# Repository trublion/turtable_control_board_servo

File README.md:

## Description

HW control board for turntable. Controls a Teknic Clearpath servo motor, reads an analog audio signal envelope.

## Links (datasheets and documentation)

[IEC plug](https://www.schurter.com/en/datasheet/typ_6765.pdf)
[Potentiometer RK09L](https://tech.alpsalpine.com/prod/e/pdf/potentiometer/rotarypotentiometers/rk09l/rk09l.pdf)  
[Neutrik combo](https://www.neutrik.com/en/product/nj3fp6c.pdf)  

[Clearpath documentation and software](https://www.teknic.com/downloads/)  
Motor user's manual : ClearPath-MC and -SD Series User manual  
Software : ClearPath-MC and -SD Series Motor Setup Program (MSP)  
Mechanical drawings : NEMA 23xx Clearpath Motor familly  
[74HCT4066](https://assets.nexperia.com/documents/data-sheet/74HC_HCT4066.pdf)
[Shunt resistors](https://www.te.com/commerce/DocumentDelivery/DDEController?Action=showdoc&DocId=Data+Sheet%7F9-1773463-7%7FG%7Fpdf%7FEnglish%7FENG_DS_9-1773463-7_G.pdf%7FCAT-C339-A76B)
[BAS21 small signal diode](https://www.vishay.com/docs/85540/bas19.pdf)
[Zener diodes](https://assets.nexperia.com/documents/data-sheet/BZX84_SER.pdf)
[Electrolytic capacitors](https://industrial.panasonic.com/cdbs/www-data/pdf/RDE0000/ABA0000C1181.pdf)
[LM358 comparator](https://www.ti.com/lit/ds/symlink/lm158-n.pdf)
[LM833 operational amplifier](https://www.ti.com/lit/ds/symlink/lm833-n.pdf)
[LM2674 DCDC controller](https://www.ti.com/lit/ds/symlink/lm2674.pdf)
[MBRS3100T3G Schottky power diode](https://www.onsemi.com/pdf/datasheet/mbrs3100t3-d.pdf)
[RS2 power diode](https://www.semiee.com/file/ELMX/MULTICOMP-RS2A.pdf)
[Power inductor](https://www.bourns.com/docs/Product-Datasheets/SRR0735A.pdf)

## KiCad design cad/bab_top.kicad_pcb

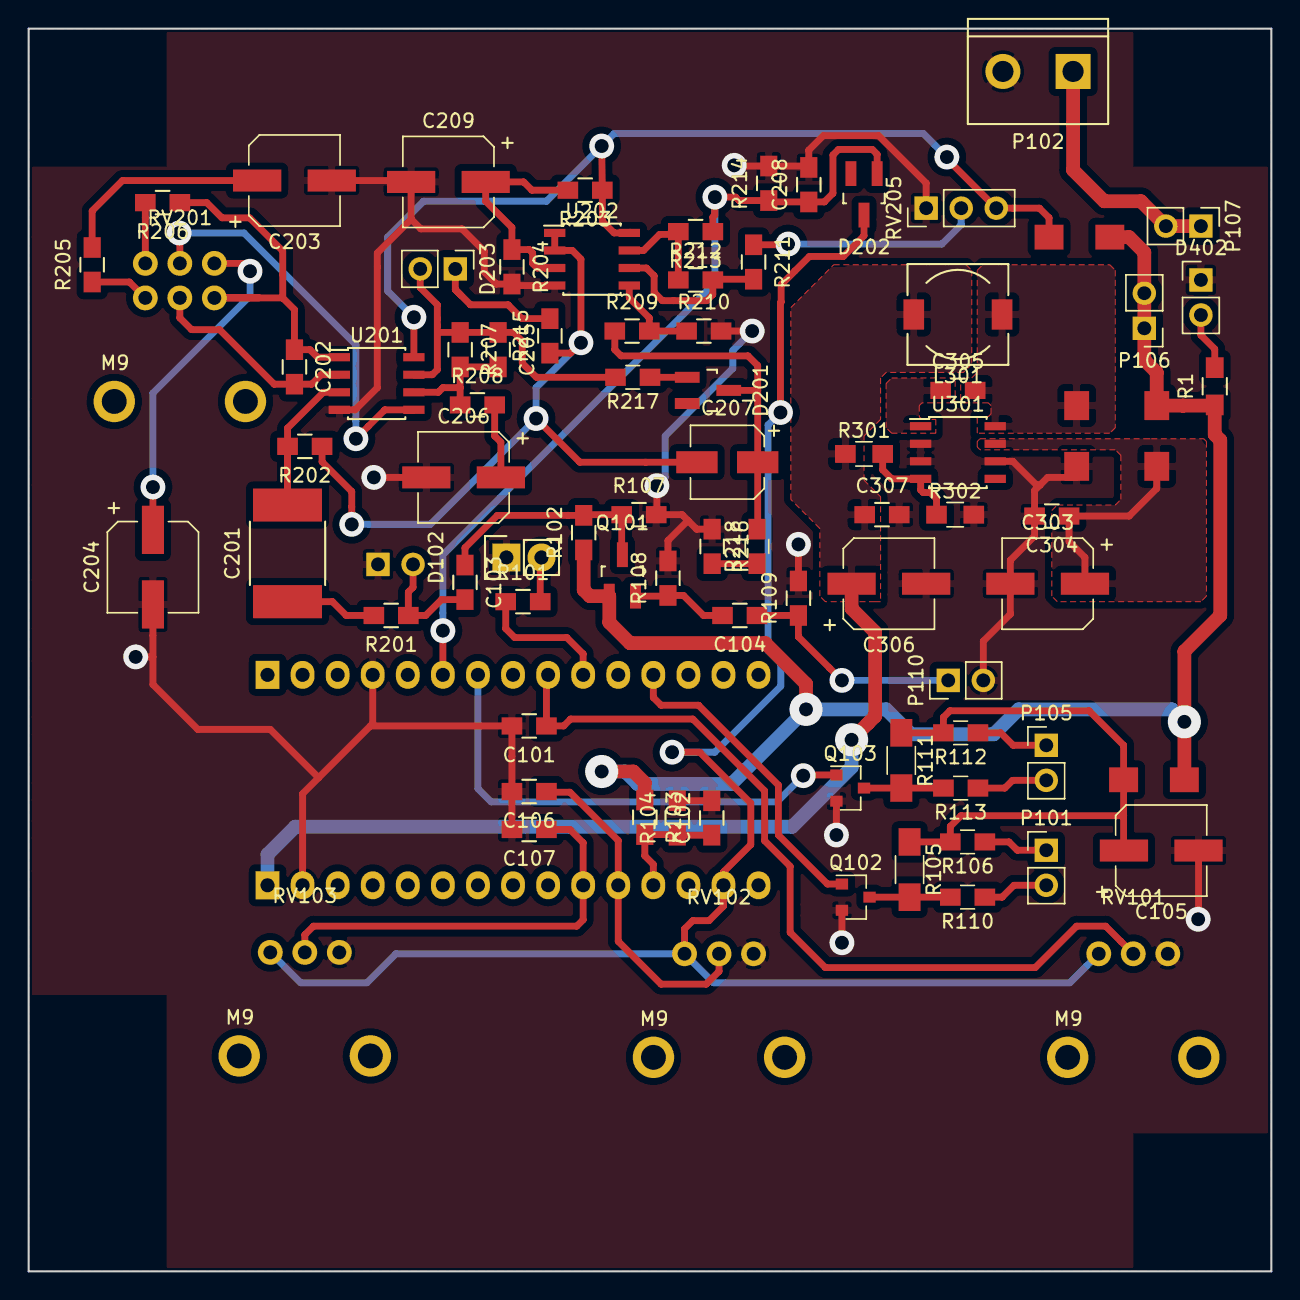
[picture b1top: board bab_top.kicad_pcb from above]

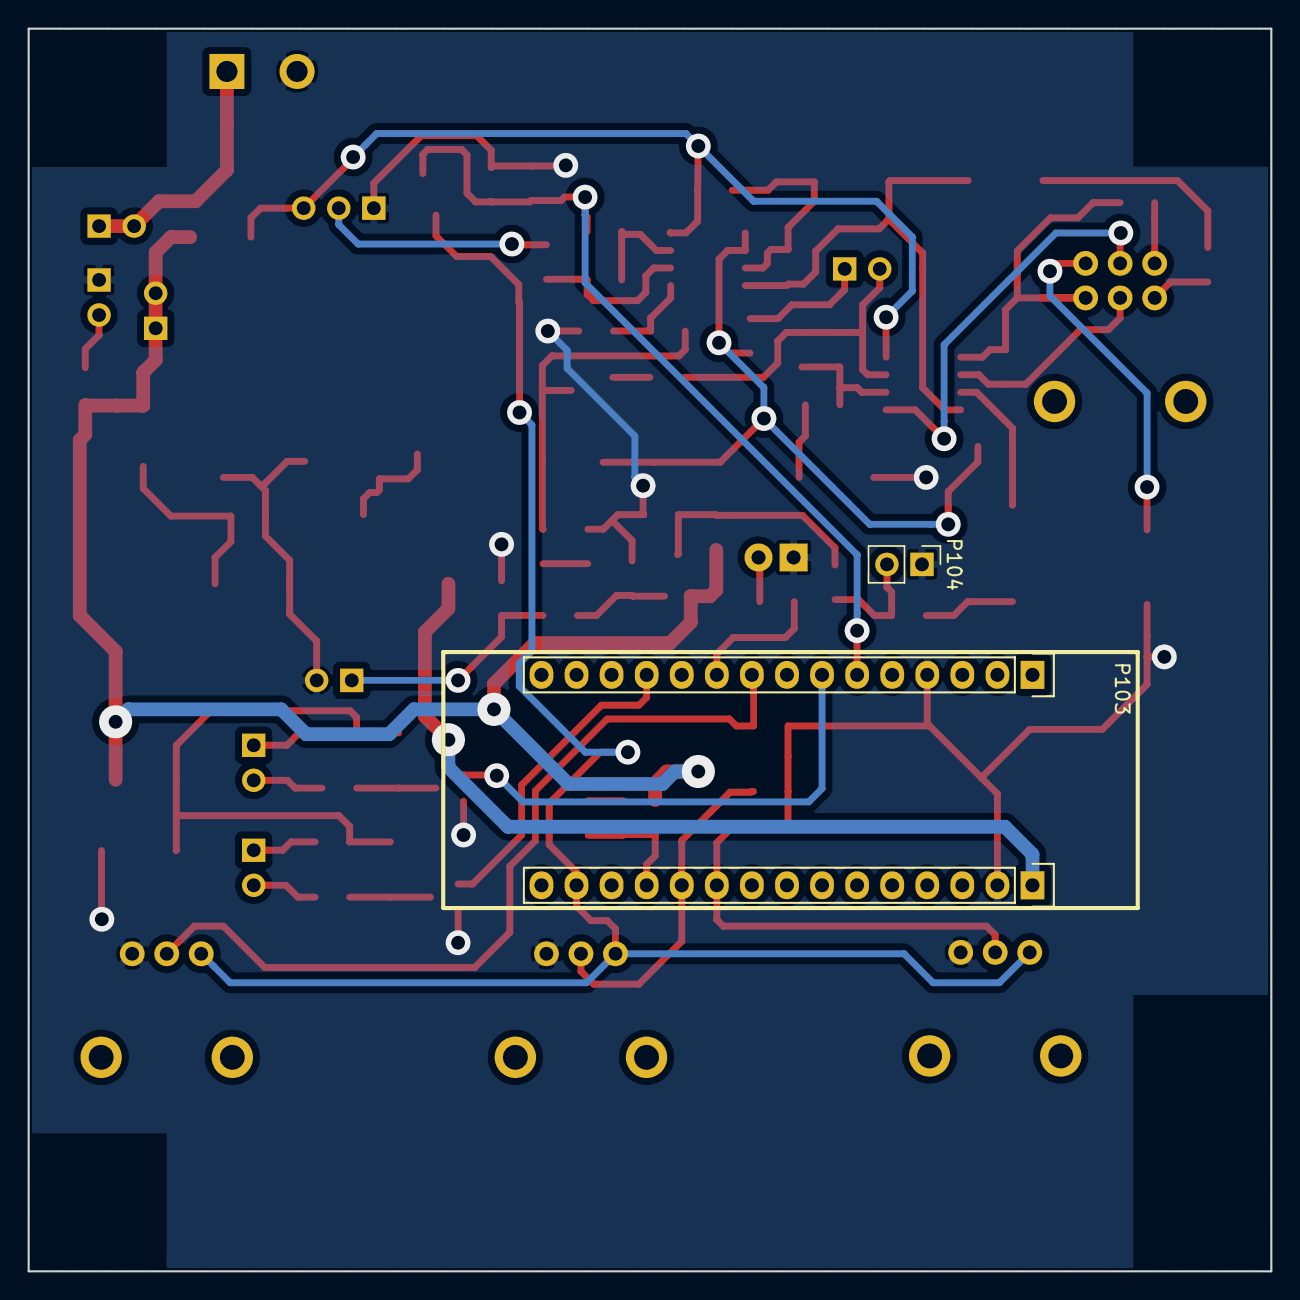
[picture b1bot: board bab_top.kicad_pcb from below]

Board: 2 copper layers, 90.0 x 90.0 mm, 84 parts (2 on the bottom side), 53 nets.

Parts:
C101, C102, C106, C107, C208, C304, C307: 100n; C_0805_HandSoldering
C103, C104: 220n; C_0805_HandSoldering
C105, C303, C306: 100u; CP_Elec_6.3x7.7
C201: 1u; C_2220_HandSoldering
C202, C205: 100p; C_0805_HandSoldering
C203, C204, C206: 47u; CP_Elec_6.3x7.7
C207: 6.8u; CP_Elec_5x5.7
C209: 10u; CP_Elec_6.3x7.7
C305: 10n; C_0805_HandSoldering
D101, D301, D302, D303: MBRS3100T3G; DO-214AC
D102: Led_Small; Pin_Header_Straight_1x02
D201, D202: BAS21; SOT-23_Handsoldering
D203, D402: Led_Small; Pin_Header_Straight_1x02_Pitch2.54mm
L301: 100u; Choke_SMD_7.3x7.3_H3.5
P101, P104, P105, P106, P107, P110: CONN_01X02; Pin_Header_Straight_1x02_Pitch2.54mm
P102: CONN_01X02; bornier2
P103: Nulceo_F303K8_CONN; Nucleo_F303K8_CONN
Q101: J201; SOT-23_Handsoldering
Q102, Q103: DTC114Y; SOT-23
R1: 1k; R_0805_HandSoldering
R101, R106, R110, R112, R113: 330; C_0805_HandSoldering
R102, R107, R202: 1M; C_0805_HandSoldering
R103, R203, R204, R209, R210, R211, R212, R213: 33k; C_0805_HandSoldering
R104, R208: 4.7k; C_0805_HandSoldering
R105, R111: 1k; C_1206_HandSoldering
R108, R214: 10k; C_0805_HandSoldering
R109: 100k; C_0805_HandSoldering
R201, R215: 1k; C_0805_HandSoldering
R205: 2k2; C_0805_HandSoldering
R206, R217: 100; C_0805_HandSoldering
R207: 75k; C_0805_HandSoldering
R216: 0; C_0805_HandSoldering
R218: 470k; C_0805_HandSoldering
R301: 47k; R_0805_HandSoldering
R302: 10k; R_0805_HandSoldering
RV101, RV102, RV103: 10k; ALPS_RK09L
RV201: RK09L_stereo; ALPS_RK09L_stereo
RV205: 100k; Pin_Header_Straight_1x03_Pitch2.54mm
U201: LM833; SOIC-8_3.9x4.9mm_Pitch1.27mm
U202: LM358; SOIC-8_3.9x4.9mm_Pitch1.27mm
U301: LM2674; SOIC-8_3.9x4.9mm_Pitch1.27mm

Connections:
+3V3: D202.3, P103.28, RV101.3, RV102.3, RV103.3
+24V: D101.2, D301.2, D302.2, P106.1, P106.2, Q101.1, R1.1, R102.1, R103.1
+VSW: C306.1, C307.1, L301.2, P103.2, R301.1
/AN_PEAK_MCU: C208.1, D202.1, P103.11, R213.1, R214.1
/AUDIO_IN: C103.2, P104.2, R201.1
/BATT_DIAG_MCU: C102.1, P103.24, R103.2, R104.1
/ENABLE_CMD_MCU: P103.13, Q103.1
/OFFSET_CONTROL_MCU: C101.1, P103.17, RV101.2
/PWM_CMD_MCU: P103.23, Q102.1
/PWM_VIS_MCU: P103.19, R101.1
/audio_bypass: C104.1, P110.1, R109.1
/v_max: C106.1, P103.22, RV102.2
/v_min: C107.1, P103.20, RV103.2
GNDA: C101.2, C102.2, C105.2, C106.2, C107.2, C203.2, C204.2, C206.2, C208.2, C209.2, C303.2, C304.2, C306.2, C307.2, D102.1, D303.2, D402.1, P102.2, P103.4, P103.7, P104.1, P110.2, Q102.2, Q103.2, R104.2, R107.2, R108.2, R109.2, R204.2, R210.2, R214.2, R216.1, R302.2, RV101.1, RV102.1, RV103.1, RV205.1, U201.4, U202.4, U301.2, U301.3, U301.6
unnamed: C103.1, Q101.3, R102.2, R107.1
unnamed: C104.2, Q101.2, R108.1
unnamed: C201.1, R201.2
unnamed: C201.2, R202.2, U201.3
unnamed: C202.1, R206.1, RV201.1, U201.1
unnamed: C202.2, RV201.2, U201.2
unnamed: C203.1, R205.2
unnamed: C204.1, RV201.4
unnamed: C205.1, D203.2, R207.1, R217.2, U201.7
unnamed: C205.2, R207.2, R208.1, U201.6
unnamed: C206.1, R208.2
unnamed: C207.1, D201.3, R209.1, R218.2
unnamed: C209.1, R203.2, R204.1, U202.3
unnamed: C305.1, U301.1
unnamed: C305.2, D303.1, L301.1, U301.8
unnamed: D102.2, R101.2
unnamed: D201.1, R217.1
unnamed: D203.1, R215.2
unnamed: D402.2, R1.2
unnamed: P101.1, R106.1
unnamed: P101.2, R110.1
unnamed: P102.1, P107.1, P107.2
unnamed: P105.1, R112.1
unnamed: P105.2, R113.1
unnamed: Q102.3, R105.2, R110.2
unnamed: Q103.3, R111.2, R113.2
unnamed: R205.1, RV201.3
unnamed: R206.2, RV201.6
unnamed: R209.2, R210.1, U202.5
unnamed: R211.1, RV205.2
unnamed: R211.2, R212.2, U202.6
unnamed: R212.1, R213.2, U202.7
unnamed: R216.2, R218.1
unnamed: R301.2, R302.1, U301.4
unnamed: RV201.5, U201.5
VAA: D302.1, R203.1, RV205.3, U201.8, U202.8
VCOM: C207.2, R202.1, R215.1, U202.1, U202.2
VDD: C303.1, C304.1, D301.1, U301.7
Vdrive: C105.1, D101.1, R105.1, R106.2, R111.1, R112.2

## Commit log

2021-04-11 Initial commit.
